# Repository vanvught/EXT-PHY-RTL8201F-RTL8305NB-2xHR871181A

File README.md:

# External PHY RTL8201F with switch RTL8305NB and 2xHR871181A

More information [https://www.gd32-dmx.org/ethernet.html](https://www.gd32-dmx.org/ethernet.html)

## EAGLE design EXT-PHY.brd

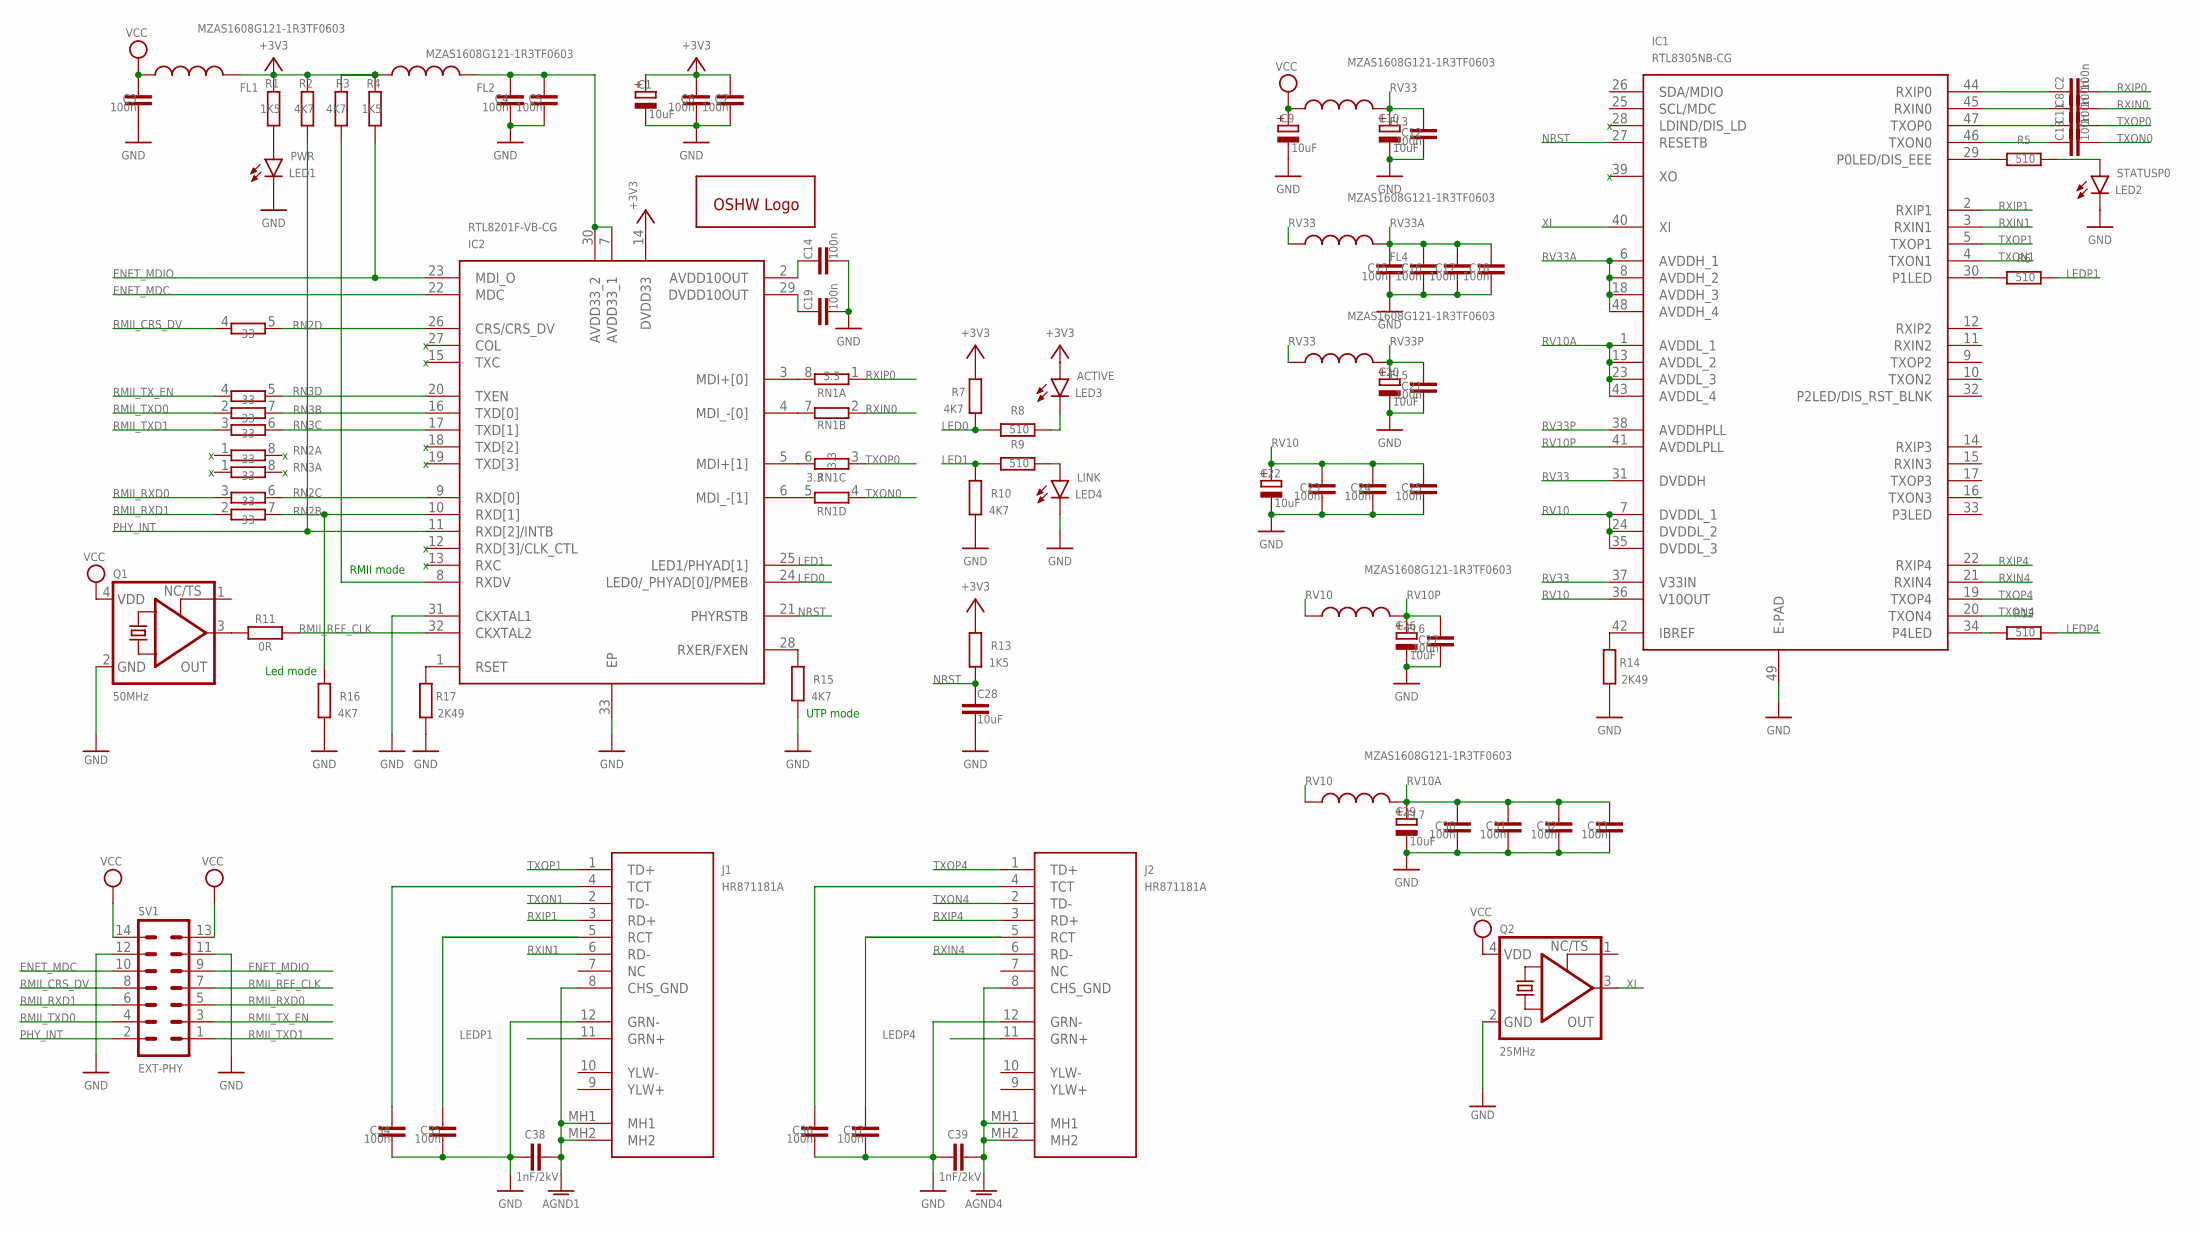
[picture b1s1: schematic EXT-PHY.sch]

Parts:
C1, C9, C10, C20, C22, C26, C29: 10uF; A/3216-18R; JLCPCB C7171
C2, C3, C4, C5, C6, C7, C8, C11, C12, C13, C14, C15, C16, C17, C18, C19, C21, C23, C24, C25, C27, C30, C31, C32, C33, C34, C35, C36, C37: 100n; C0402; JLCPCB C1525
C28: 10uF; C0603; JLCPCB C19702
C38, C39: 1nF/2kV; C1206; JLCPCB C9196
FL1, FL2, FL3, FL4, FL5, FL6, FL7: MZAS1608G121-1R3TF0603; 0603
GOLD_ORB_SM1: OSHWLOGOLOGO5MM; OSHW_5MM
IC1: RTL8305NB-CG; QFN40P600X600X100-49N
IC2: RTL8201F-VB-CG; QFN50P500X500X100-33N; JLCPCB C45044
J1, J2: HR871181A
LED1: PWR; CHIP-LED0603; JLCPCB C72043
LED2: STATUSP0; CHIP-LED0603; JLCPCB C72043
LED3: ACTIVE; CHIP-LED0603; JLCPCB C72043
LED4: LINK; CHIP-LED0603; JLCPCB C72043
Q1: 50MHz; 3.2X2.5_KXO-V96; JLCPCB C160451
Q2: 25MHz; 3.2X2.5_KXO-V96; JLCPCB C160454
R1, R4, R13: 1K5; R0603; JLCPCB C22843
R2, R3, R7, R10, R15, R16: 4K7; R0603; JLCPCB C23162
R5, R6, R8, R9, R12: 510; R0603; JLCPCB C23193
R11: 0R; R0603; JLCPCB C115304
R14, R17: 2K49; R0603; JLCPCB C100897
RN1: 3.3; 4X0402ARV341; JLCPCB C728736
RN2, RN3: 33; 4X0402ARV341; JLCPCB C25501
SV1: EXT-PHY; MA07-2W

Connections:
50MHZ: Q1.3 (OUT), R11.1
+3V3: C1.+, C6.2, C7.2, FL1.2, FL2.1, IC2.14 (DVDD33), LED3.A, R1.2, R2.2, R3.1, R4.2, R7.2, R13.2
AGND1: C38.2, J1.8 (CHS_GND), J1.MH1, J1.MH2
AGND4: C39.2, J2.8 (CHS_GND), J2.MH1, J2.MH2
AVDD: C4.2, C5.2, FL2.2, IC2.7 (AVDD33_1), IC2.30 (AVDD33_2)
ENET_MDC: IC2.22 (MDC), SV1.10
ENET_MDIO: IC2.23 (MDI_O), R4.1, SV1.9
GND: C1.-, C3.1, C4.1, C5.1, C6.1, C7.1, C9.-, C10.-, C12.1, C14.2, C15.1, C16.1, C17.1, C18.1, C19.2, C20.-, C21.1, C22.-, C23.1, C24.1, C25.1, C26.-, C27.1, C28.2, C29.-, C30.1, C31.1, C32.1, C33.1, C34.1, C35.1, C36.1, C37.1, C38.1, C39.1, IC1.49 (E-PAD), IC2.31 (CKXTAL1), IC2.33 (EP), J1.12 (GRN-), J2.12 (GRN-), LED1.C, LED2.C, LED4.C, Q1.2 (GND), Q2.2 (GND), R10.1, R14.2, R15.1, R16.1, R17.2, SV1.11, SV1.12
LED0: IC2.24 (LED0/_PHYAD[0]/PMEB), R7.1, R8.2
LED1: IC2.25 (LED1/PHYAD[1]), R9.2, R10.2
LEDP1: J1.11 (GRN+), R6.1
LEDP4: J2.11 (GRN+), R12.1
unnamed: LED1.A, R1.1
unnamed: C37.2, J2.5 (RCT)
unnamed: C36.2, J2.4 (TCT)
unnamed: IC2.1 (RSET), R17.1
unnamed: IC2.8 (RXDV), R3.2
unnamed: C14.1, IC2.2 (AVDD10OUT)
unnamed: IC2.28 (RXER/FXEN), R15.2
unnamed: IC1.42 (IBREF), R14.1
unnamed: C35.2, J1.5 (RCT)
unnamed: C34.2, J1.4 (TCT)
unnamed: C19.1, IC2.29 (DVDD10OUT)
unnamed: IC1.30 (P1LED), R6.2
unnamed: IC1.34 (P4LED), R12.2
unnamed: IC2.3 (MDI+[0]), RN1.8 (2)
unnamed: LED3.C, R8.1
unnamed: IC2.4 (MDI_-[0]), RN1.7 (2)
unnamed: IC2.5 (MDI+[1]), RN1.6 (2)
unnamed: IC2.6 (MDI_-[1]), RN1.5 (2)
unnamed: LED2.A, R5.1
unnamed: IC1.29 (P0LED/DIS_EEE), R5.2
unnamed: C13.1, IC1.46 (TXON0)
unnamed: C11.1, IC1.47 (TXOP0)
unnamed: C8.1, IC1.45 (RXIN0)
unnamed: C2.1, IC1.44 (RXIP0)
unnamed: LED4.A, R9.1
NRST: C28.1, IC1.27 (RESETB), IC2.21 (PHYRSTB), R13.1
PHY_INT: IC2.11 (RXD[2]/INTB), R2.1, SV1.2
RMII_CRS_DV: RN2.4 (1), SV1.8
RMII_REF_CLK: IC2.32 (CKXTAL2), R11.2, SV1.7
RMII_RXD0: RN2.3 (1), SV1.5
RMII_RXD1: RN2.2 (1), SV1.6
RMII_TXD0: RN3.2 (1), SV1.4
RMII_TXD1: RN3.3 (1), SV1.1
RMII_TX_EN: RN3.4 (1), SV1.3
RV10: C22.+, C23.2, C24.2, C25.2, FL6.1, FL7.1, IC1.7 (DVDDL_1), IC1.24 (DVDDL_2), IC1.35 (DVDDL_3), IC1.36 (V10OUT)
RV10A: C29.+, C30.2, C31.2, C32.2, C33.2, FL7.2, IC1.1 (AVDDL_1), IC1.13 (AVDDL_2), IC1.23 (AVDDL_3), IC1.43 (AVDDL_4)
RV10P: C26.+, C27.2, FL6.2, IC1.41 (AVDDLPLL)
RV33: C10.+, C12.2, FL3.2, FL4.1, FL5.1, IC1.31 (DVDDH), IC1.37 (V33IN)
RV33A: C15.2, C16.2, C17.2, C18.2, FL4.2, IC1.6 (AVDDH_1), IC1.8 (AVDDH_2), IC1.18 (AVDDH_3), IC1.48 (AVDDH_4)
RV33P: C20.+, C21.2, FL5.2, IC1.38 (AVDDHPLL)
RXD0: IC2.9 (RXD[0]), RN2.6 (2)
RXD1: IC2.10 (RXD[1]), R16.2, RN2.7 (2)
RXDV: IC2.26 (CRS/CRS_DV), RN2.5 (2)
RXIN0: C8.2, RN1.2 (1)
RXIN1: IC1.3 (RXIN1), J1.6 (RD-)
RXIN4: IC1.21 (RXIN4), J2.6 (RD-)
RXIP0: C2.2, RN1.1
RXIP1: IC1.2 (RXIP1), J1.3 (RD+)
RXIP4: IC1.22 (RXIP4), J2.3 (RD+)
TXD0: IC2.16 (TXD[0]), RN3.7 (2)
TXD1: IC2.17 (TXD[1]), RN3.6 (2)
TXEN: IC2.20 (TXEN), RN3.5 (2)
TXON0: C13.2, RN1.4 (1)
TXON1: IC1.4 (TXON1), J1.2 (TD-)
TXON4: IC1.20 (TXON4), J2.2 (TD-)
TXOP0: C11.2, RN1.3 (1)
TXOP1: IC1.5 (TXOP1), J1.1 (TD+)
TXOP4: IC1.19 (TXOP4), J2.1 (TD+)
VCC: C3.2, C9.+, FL1.1, FL3.1, Q1.4 (VDD), Q2.4 (VDD), SV1.13, SV1.14
XI: IC1.40 (XI), Q2.3 (OUT)

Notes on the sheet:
RMII mode
UTP mode
Led mode

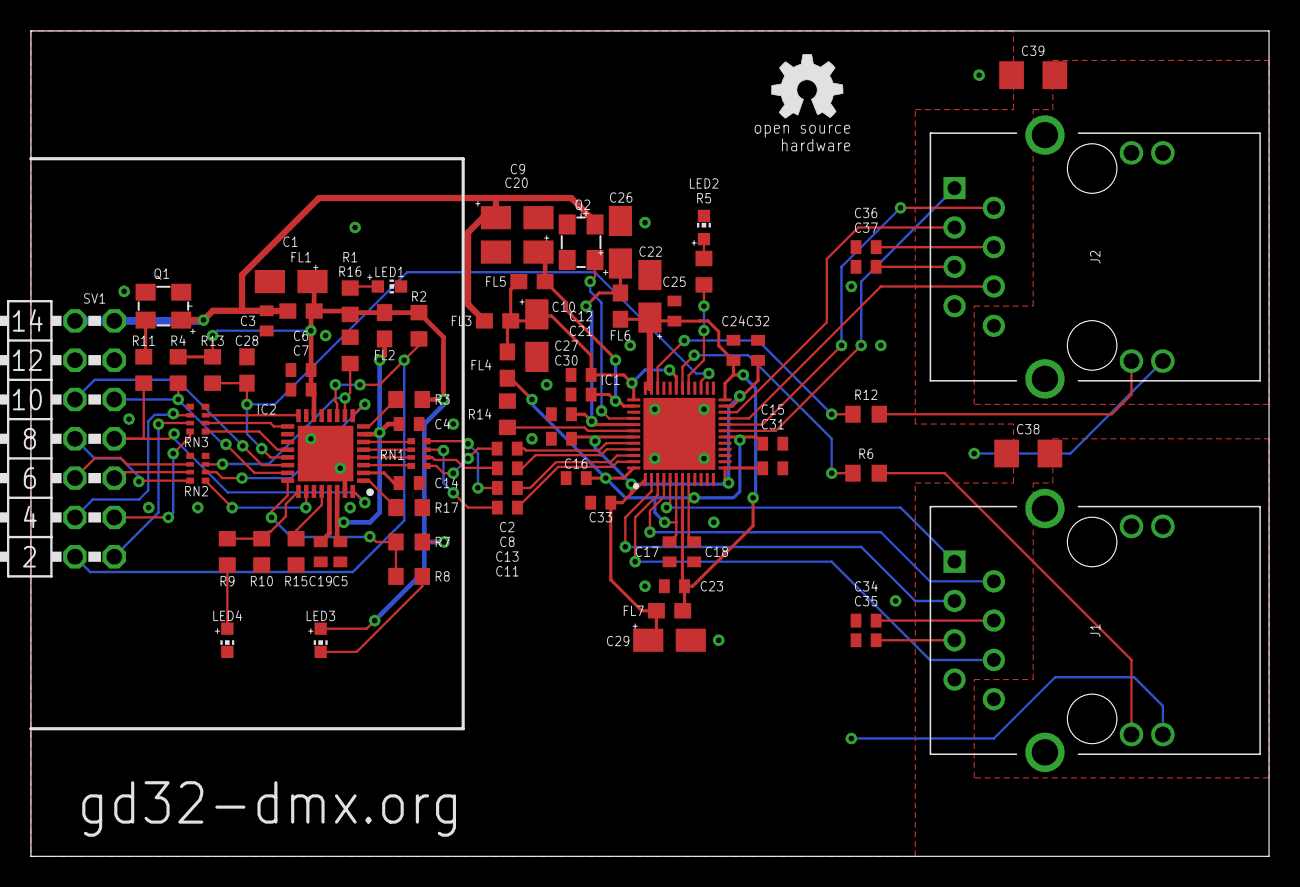
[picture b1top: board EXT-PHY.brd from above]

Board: 2 copper layers, 80.0 x 53.3 mm, 78 parts (0 on the bottom side), 72 nets.

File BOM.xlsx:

Qty | Designator | Footprint | Comment | LCSC Part # | Original
7 | C1, C9, C10, C20, C22, C26, C29 | A/3216-18R | 10uF | C7171
29 | C2, C3, C4, C5, C6, C7, C8, C11, C12, C13, C14, C15, C16, C17, C18, C19, C21, C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 | C0402 | 100n | C1525
1 | C28 | C0603 | 10uF | C19702
2 | C38, C39 | C1206 | 1nF/2kV | C9196
7 | FL1, FL2, FL3, FL4, FL5, FL6, FL7 | 603 | MZAS1608G121-1R3TF | C709642
1 | IC1 | QFN40P600X600X100-49N | RTL8305NB-CG | C3010343
1 | IC2 | QFN50P500X500X100-33N | RTL8201F-VB-CG | C45044
2 | J1, J2 | HR871181A | HR871181A | C49312
1 | LED1 | CHIP-LED0603 | PWR | C72043
1 | LED2 | CHIP-LED0603 | STATUSP0 | C72043
1 | LED3 | CHIP-LED0603 | ACTIVE | C72043
1 | LED4 | CHIP-LED0603 | LINK | C72043
1 | Q1 | 3.2X2.5_KXO-V96 | 50MHz | C160451
1 | Q2 | 3.2X2.5_KXO-V96 | 25MHz | C295525 | C160454
3 | R1, R4, R13 | R0603 | 1K5 | C22843
1 | R11 | R0603 | 0R | C115304
2 | R14, R17 | R0603 | 2K49 | C100897
6 | R2, R3, R7, R10, R15, R16 | R0603 | 4K7 | C23162
5 | R5, R6, R8, R9, R12 | R0603 | 510 | C23193
1 | RN1 | 4X0402ARV341 | 3.3 | C728736
2 | RN2, RN3 | 4X0402ARV341 | 33 | C25501

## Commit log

2024-03-03 Initial commit
    @particlerain

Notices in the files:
parts and their libraries:
crystal-geyer_V1_0: Copyright: Geyer-Electronic
